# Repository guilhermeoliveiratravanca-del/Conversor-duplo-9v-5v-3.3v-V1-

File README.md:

# Conversor Duplo de Voltagem (9V para 5V e 3.3V) - V1

Este projeto consiste num conversor duplo de tensão utilizando reguladores lineares para rebaixar uma entrada de **9V** para duas saídas estáveis: **5V** (via conector USB-A) e **3.3V** (via terminal de parafusos). É ideal para alimentar placas de desenvolvimento como Arduino e ESP32.

## Dados Teóricos de Potência e Temperatura

Abaixo encontram-se os cálculos efetuados para analisar o comportamento térmico dos reguladores sob diferentes condições de carga, considerando uma **Temperatura Ambiente de 25°C**:

### Regulador de 5V (LM7805)

| Vi (V) | Vo (V) | I (A) | P (W) | Rθja (°C/W) | Rθjc (°C/W) | Ttnu (°C) | Ttcom (°C) |
|:---:|:---:|:---:|:---:|:---:|:---:|:---:|:---:|
| 9 | 5 | 0.5 | 2.0 | 50 | 21 | 125 | 78 |
| 9 | 5 | 0.8 | 3.2 | 50 | 21 | 185 | 109.8 |
| 9 | 5 | 0.5 | 2.0 | 50 | 16 | 125 | 68 |
| 9 | 5 | 0.8 | 3.2 | 50 | 16 | 185 | 93.8 |

### Regulador de 3.3V (LD1117V33)

| Vi (V) | Vo (V) | I (A) | P (W) | Rθja (°C/W) | Rθjc (°C/W) | Ttnu (°C) | Ttcom (°C) |
|:---:|:---:|:---:|:---:|:---:|:---:|:---:|:---:|
| 5 | 3.3 | 0.3 | 0.51 | 50 | 16 | 50.5 | 35.965 |
| 9 | 3.3 | 0.3 | 1.71 | 50 | 16 | 110.5 | 61.765 |
| 5 | 3.3 | 0.3 | 0.51 | 50 | 21 | 50.5 | 38.515 |
| 9 | 3.3 | 0.3 | 1.71 | 50 | 21 | 110.5 | 70.315 |

*Nota: **Ttnu** representa a temperatura estimada do componente sem dissipador (nú), e **Ttcom** com  dissipador térmico externo.

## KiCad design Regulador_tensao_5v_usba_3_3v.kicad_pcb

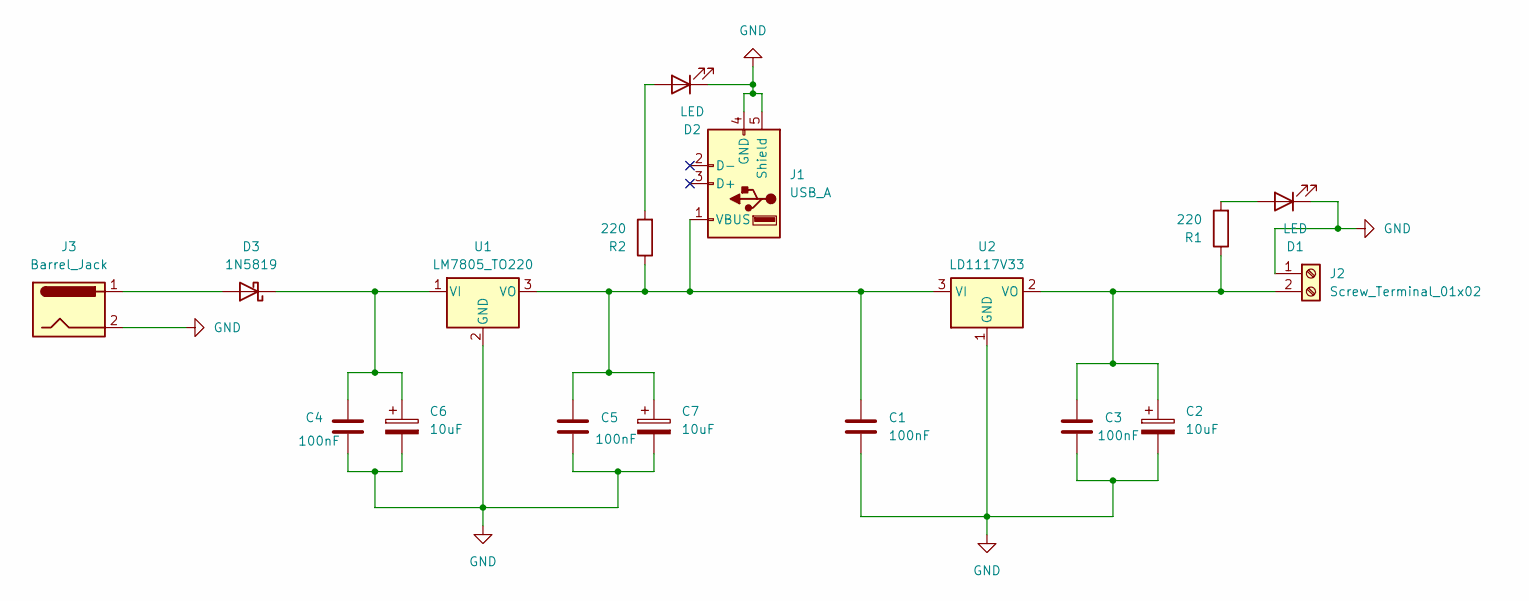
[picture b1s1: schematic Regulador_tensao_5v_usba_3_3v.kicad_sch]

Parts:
C1, C3, C4, C5: 100nF; C_Disc_D5.0mm_W2.5mm_P5.00mm
C2, C6, C7: 10uF; CP_Radial_D5.0mm_P2.00mm
D1, D2: LED; LED_D5.0mm
D3: 1N5819; D_DO-41_SOD81_P10.16mm_Horizontal
J1: USB_A; USB_A_Wuerth_614004134726_Horizontal
J2: Screw_Terminal_01x02; TerminalBlock_Phoenix_PT-1,5-2-3.5-H_1x02_P3.50mm_Horizontal
J3: Barrel_Jack; BarrelJack_Horizontal
R1, R2: 220; R_Axial_DIN0207_L6.3mm_D2.5mm_P10.16mm_Horizontal
U1: LM7805_TO220; TO-220-3_Vertical
U2: LD1117V33; TO-220-3_Vertical

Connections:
GND: C1.2, C2.2, C3.2, C4.2, C5.2, C6.2, C7.2, D1.1 (K), D2.1 (K), J1.4 (GND), J1.5 (Shield), J2.1, J3.2, U1.2 (GND), U2.1 (GND)
unnamed: D1.2 (A), R1.2
unnamed: D2.2 (A), R2.2
unnamed: D3.2 (A), J3.1
unnamed: C4.1, C6.1, D3.1 (K), U1.1 (VI)
unnamed: C1.1, C5.1, C7.1, J1.1 (VBUS), R2.1, U1.3 (VO), U2.3 (VI)
unnamed: C2.1, C3.1, J2.2, R1.1, U2.2 (VO)

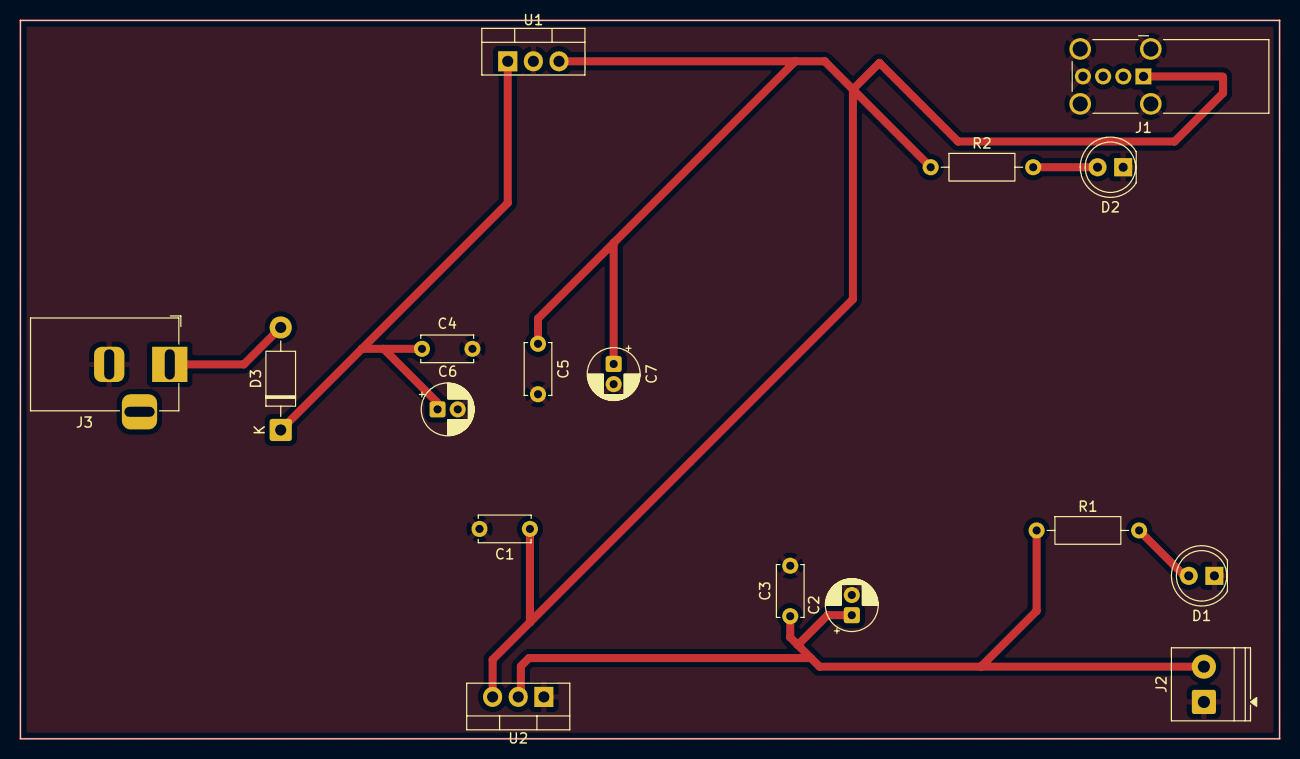
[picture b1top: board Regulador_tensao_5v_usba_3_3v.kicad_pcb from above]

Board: 2 copper layers, 124.8 x 71.2 mm, 17 parts (0 on the bottom side), 7 nets.
